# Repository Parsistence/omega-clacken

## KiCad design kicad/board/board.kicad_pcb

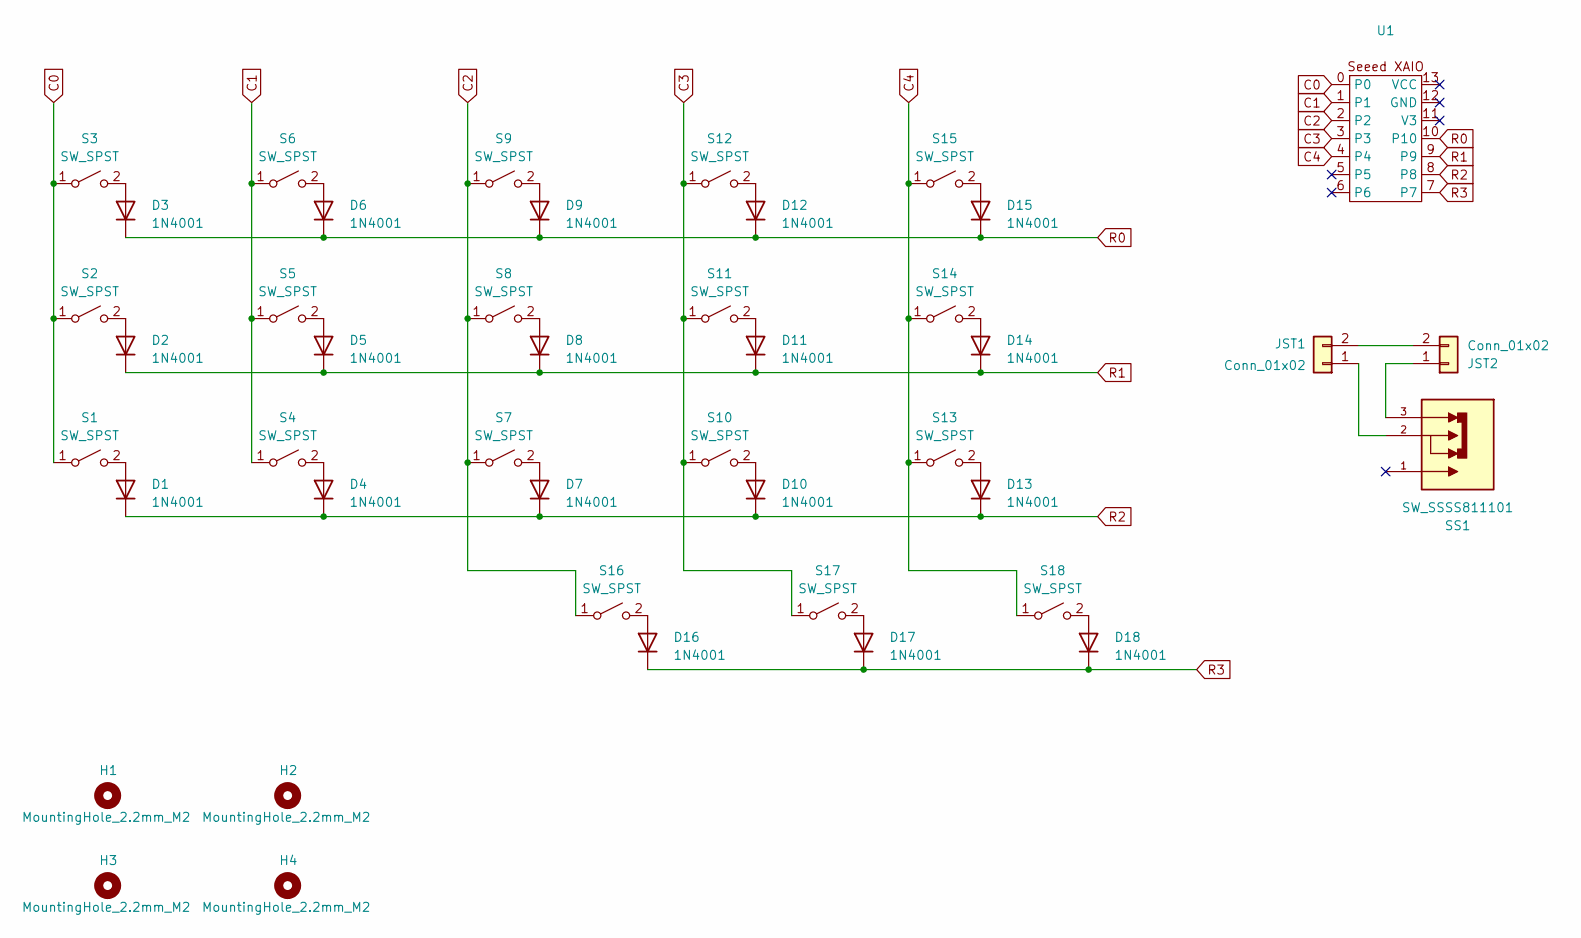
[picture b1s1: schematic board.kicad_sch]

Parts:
D1, D2, D3, D4, D5, D6, D7, D8, D9, D10, D11, D12, D13, D14, D15, D16, D17, D18: 1N4001; reversable_diode
H1, H2, H3, H4: MountingHole_2.2mm_M2
JST1, JST2: Conn_01x02; JST_angled
S1, S2, S3, S4, S5, S6, S7, S8, S9, S10, S11, S12, S13, S14, S15, S16, S17, S18: SW_SPST; choc_switches
SS1: SW_SSSS811101; PARTREV N/A
U1: seeed_xaio

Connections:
C0: S1.1 (A), S2.1 (A), S3.1 (A), U1.0
C1: S4.1 (A), S5.1 (A), S6.1 (A), U1.1
C2: S7.1 (A), S8.1 (A), S9.1 (A), S16.1 (A), U1.2
C3: S10.1 (A), S11.1 (A), S12.1 (A), S17.1 (A), U1.3
C4: S13.1 (A), S14.1 (A), S15.1 (A), S18.1 (A), U1.4
unnamed: D1.2 (A), S1.2 (B)
unnamed: D2.2 (A), S2.2 (B)
unnamed: D3.2 (A), S3.2 (B)
unnamed: D4.2 (A), S4.2 (B)
unnamed: D5.2 (A), S5.2 (B)
unnamed: D6.2 (A), S6.2 (B)
unnamed: D7.2 (A), S7.2 (B)
unnamed: D8.2 (A), S8.2 (B)
unnamed: D9.2 (A), S9.2 (B)
unnamed: D10.2 (A), S10.2 (B)
unnamed: D11.2 (A), S11.2 (B)
unnamed: D12.2 (A), S12.2 (B)
unnamed: D13.2 (A), S13.2 (B)
unnamed: D14.2 (A), S14.2 (B)
unnamed: D15.2 (A), S15.2 (B)
unnamed: D16.2 (A), S16.2 (B)
unnamed: D17.2 (A), S17.2 (B)
unnamed: D18.2 (A), S18.2 (B)
unnamed: JST1.1, SS1.2
unnamed: JST1.2, JST2.2
unnamed: JST2.1, SS1.3
R0: D3.1 (K), D6.1 (K), D9.1 (K), D12.1 (K), D15.1 (K), U1.10
R1: D2.1 (K), D5.1 (K), D8.1 (K), D11.1 (K), D14.1 (K), U1.9
R2: D1.1 (K), D4.1 (K), D7.1 (K), D10.1 (K), D13.1 (K), U1.8
R3: D16.1 (K), D17.1 (K), D18.1 (K), U1.7

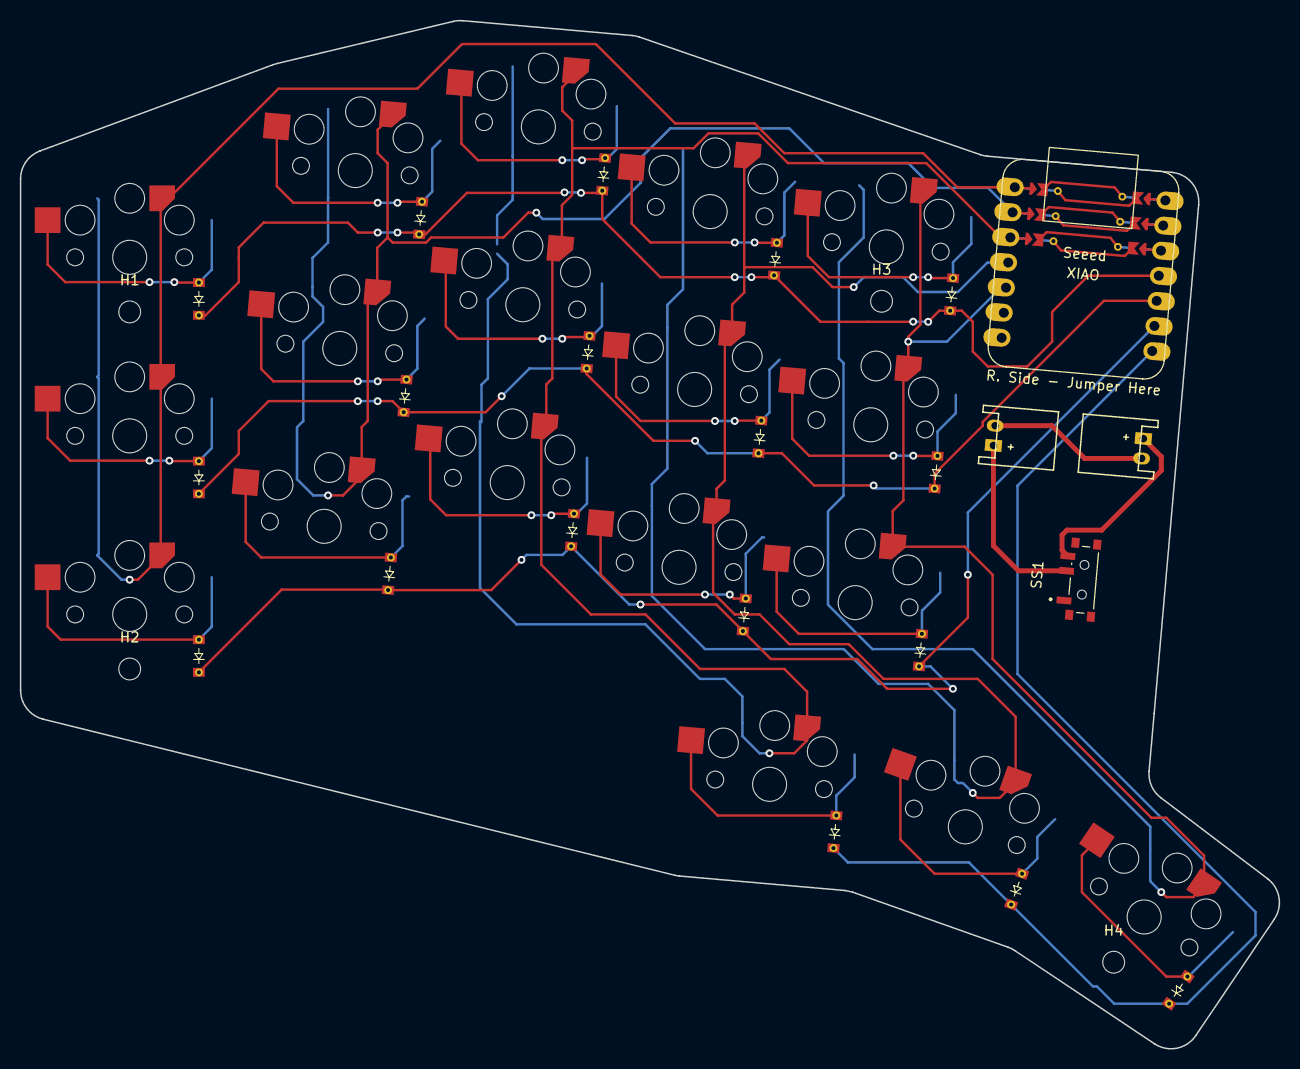
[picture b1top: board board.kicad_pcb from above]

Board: 2 copper layers, 126.9 x 103.7 mm, 44 parts (0 on the bottom side), 30 nets.

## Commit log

2024-11-16 Complete Schematic and Work on PCB Tracings
    Schematic should be complete, and most tracings are completed as well. Still some tracings left and design check still needs to be done.
2024-11-16 Finished PCB traces
